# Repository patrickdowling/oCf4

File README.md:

# OC + F4
For grins I made an F405-based Teensy replacement for [o\_C](https://github.com/patrickdowling/O_C).

It seemed like a good idea at the time and was an "excuse" to add F4 support to my F0 framework which then became
[stm32x](https://github.com/patrickdowling/stm32x).

The four-layer board is pretty tightly packed and tried to include everything and the kitchen sink (I2C, serial/MIDI, USB header...). There's even space for an SPI flash chip on the bottom... It should also be noted that I'm really just winging it when it comes to hardware design.

The single point of annoyance (the shared SPI between the DAC and screen) however remains although it is possible to run the thing at closer to 30KHz here (the Teensy 3.2 on `o_C` was effectively maxxing out at 16.6KHz with the 30MHz SPI).

Utlimately though, once the base drivers (ADC/TR/DAC/screen) were working it didn't actually have a purpose so there's very little actual functionality. Except a very early draft of what might be a "better" framework. So here it is anyway, warts
and all.

If someone does want to pursue this further, let me know.

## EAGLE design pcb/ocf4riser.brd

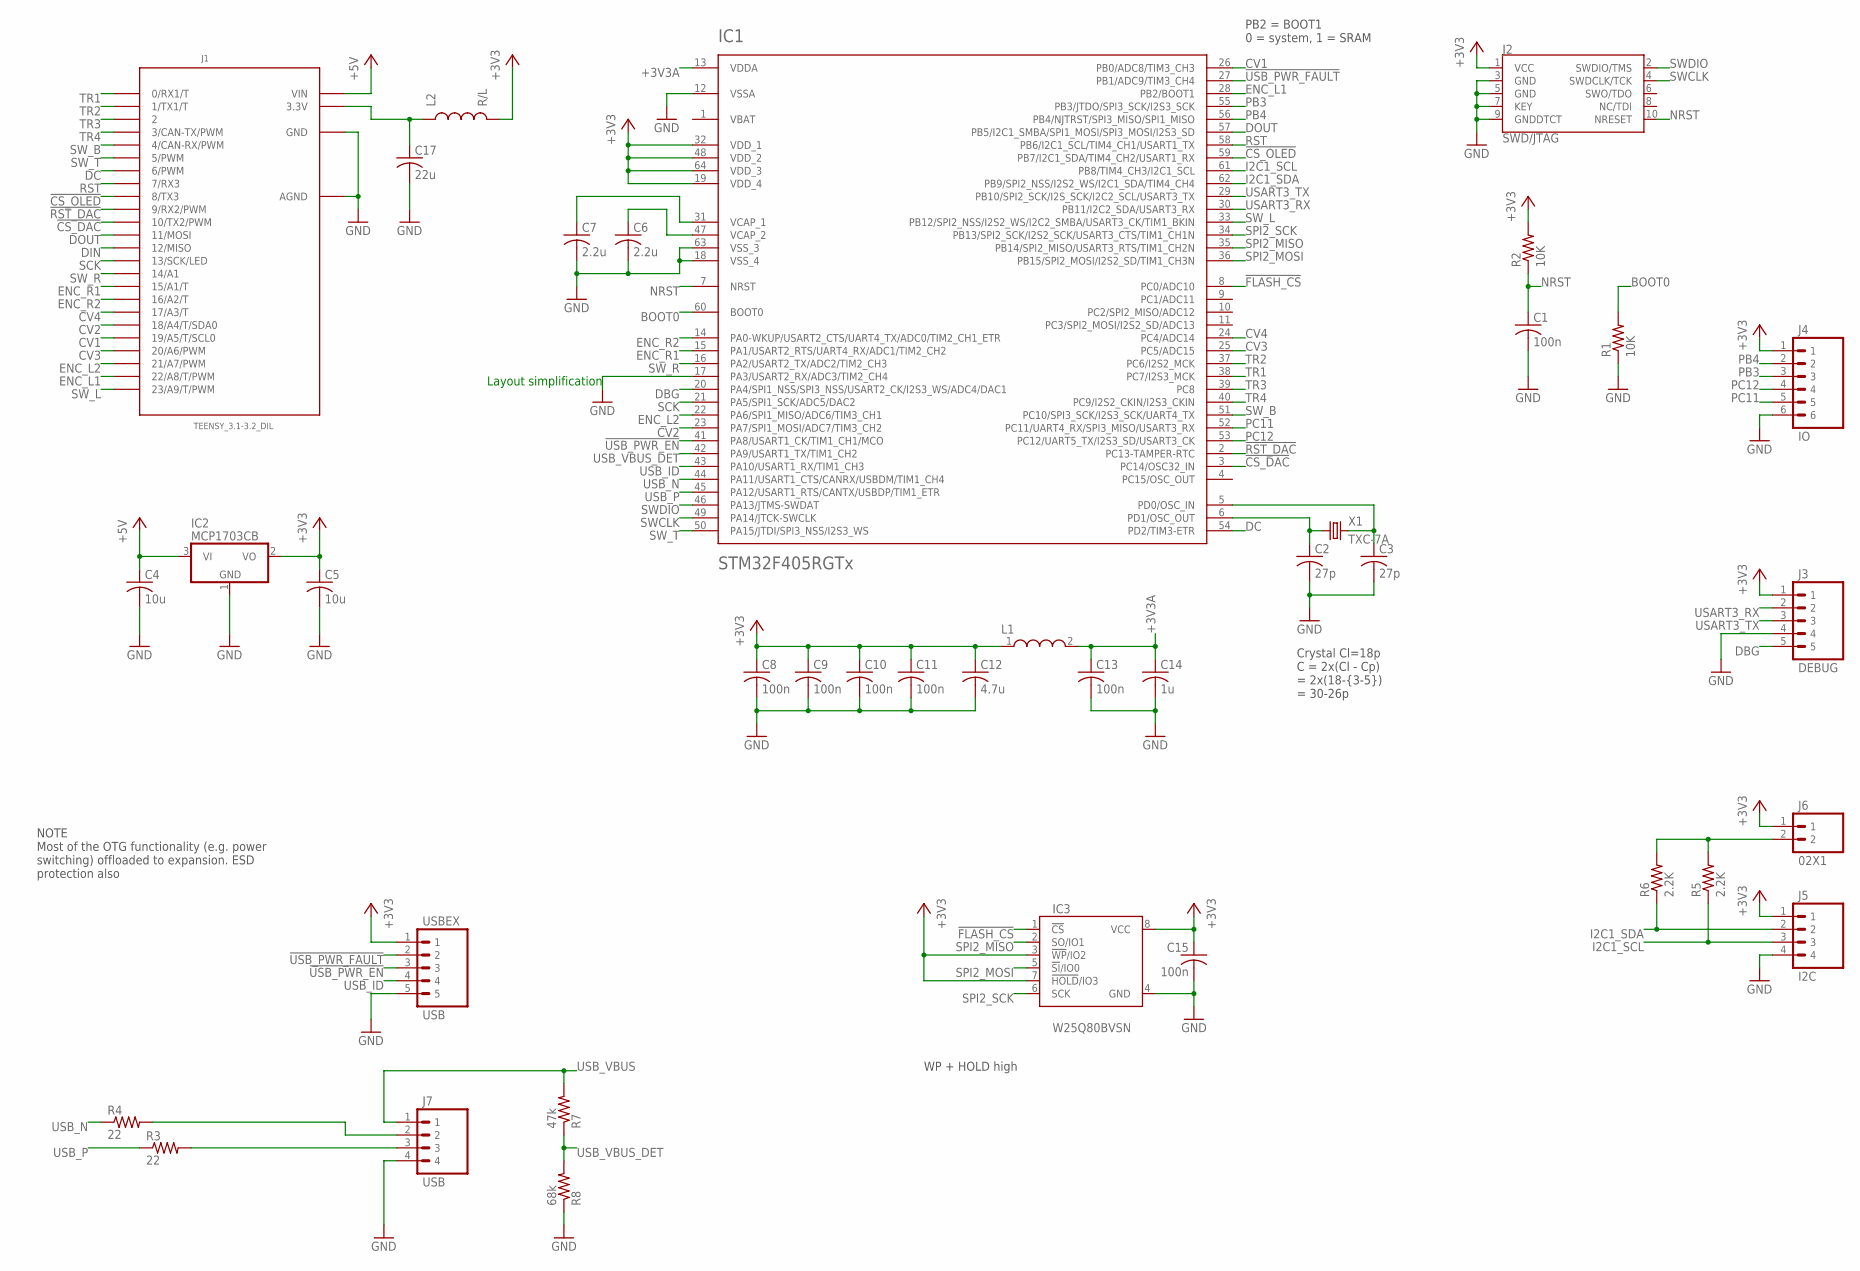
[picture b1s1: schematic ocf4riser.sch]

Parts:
C1, C8, C9, C10, C11, C13, C15: 100n; C0402
C2, C3: 27p; C0402
C4, C5: 10u; C0805
C6, C7: 2.2u; C0603
C12: 4.7u; C0603
C14: 1u; C0603
C17: 22u; C0805
IC1: STM32F405RGTx; TQFP-10X10-64
IC2: MCP1703CB; SOT23
IC3: W25Q80BVSN; SOIC-8
J1: TEENSY_3.1-3.2_DIL; TEENSY_3.0-3.2&LC_DIL
J2: SWD/JTAG; 2X5-1.27
J3: DEBUG; 05X1-THIN
J4: IO; 06X1-THIN
J5: I2C; 04X1-THIN
J6: 02X1; 02X1-THIN
J7: USB; 04X1-THIN
L1: WE-CBF_0603(WB/HS); WE-CBF_0603(W=2.2)
L2: R/L; 0805
R1, R2: 10K; R0402
R3, R4: 22; R0402
R5, R6: 2.2K; R0603
R7: 47k; R0402
R8: 68k; R0402
USBEX: USB; 05X1-THIN
X1: TXC-7A; CRYSTAL-TXC-7A

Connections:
!CS_DAC: IC1.3 (PC14/OSC32_IN), J1.10 (10/TX2/PWM)
!CS_OLED: IC1.59 (PB7/I2C1_SDA/TIM4_CH2/USART1_RX), J1.8 (8/TX3)
!FLASH_CS: IC1.8 (PC0/ADC10), IC3.1 (!CS!)
!RST_DAC: IC1.2 (PC13-TAMPER-RTC), J1.9 (9/RX2/PWM)
!USB_PWR_EN: IC1.41 (PA8/USART1_CK/TIM1_CH1/MCO), USBEX.3
!USB_PWR_FAULT: IC1.27 (PB1/ADC9/TIM3_CH4), USBEX.2
+3V3: C5.1, C8.1, C9.1, C10.1, C11.1, C12.1, C15.1, IC1.19 (VDD_4), IC1.32 (VDD_1), IC1.48 (VDD_2), IC1.64 (VDD_3), IC2.2 (VO), IC3.3 (!WP!/IO2), IC3.7 (!HOLD!/IO3), IC3.8 (VCC), J2.1 (VCC), J3.1, J4.1, J5.1, J6.1, L1.1, L2.2, R2.2, USBEX.1
+3V3A: C13.1, C14.1, IC1.13 (VDDA), L1.2
+5V: C4.1, IC2.3 (VI), J1.VIN
BOOT0: IC1.60 (BOOT0), R1.2
CV1: IC1.26 (PB0/ADC8/TIM3_CH3), J1.19/A5 (19/A5/T/SCL0)
CV2: IC1.23 (PA7/SPI1_MOSI/ADC7/TIM3_CH2), J1.18/A4 (18/A4/T/SDA0)
CV3: IC1.25 (PC5/ADC15), J1.20/A6 (20/A6/PWM)
CV4: IC1.24 (PC4/ADC14), J1.17/A3 (17/A3/T)
DBG: IC1.20 (PA4/SPI1_NSS/SPI3_NSS/USART2_CK/I2S3_WS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), J3.5
DC: IC1.54 (PD2/TIM3-ETR), J1.6 (6/PWM)
DIN: J1.12 (12/MISO)
DOUT: IC1.57 (PB5/I2C1_SMBA/SPI1_MOSI/SPI3_MOSI/I2S3_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), J1.11 (11/MOSI)
ENC_L1: IC1.28 (PB2/BOOT1), J1.22/A8 (22/A8/T/PWM)
ENC_L2: IC1.22 (PA6/SPI1_MISO/ADC6/TIM3_CH1), J1.21/A7 (21/A7/PWM)
ENC_R1: IC1.15 (PA1/USART2_RTS/UART4_RX/ADC1/TIM2_CH2), J1.15/A1 (15/A1/T)
ENC_R2: IC1.14 (PA0-WKUP/USART2_CTS/UART4_TX/ADC0/TIM2_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), J1.16/A2 (16/A2/T)
GND: C1.2, C2.2, C3.2, C4.2, C5.2, C6.2, C7.2, C8.2, C9.2, C10.2, C11.2, C12.2, C13.2, C14.2, C15.2, C17.2, IC1.12 (VSSA), IC1.17 (PA3/USART2_RX/ADC3/TIM2_CH4), IC1.18 (VSS_4), IC1.63 (VSS_3), IC2.1 (GND), IC3.4 (GND), J1.AGND, J1.GND, J2.3 (GND), J2.5 (GND), J2.7 (KEY), J2.9 (GNDDTCT), J3.4, J4.6, J5.4, J7.4, R1.1, R8.1, USBEX.5
I2C1_SCL: IC1.61 (PB8/TIM4_CH3/I2C1_SCL), J5.3, R5.1
I2C1_SDA: IC1.62 (PB9/SPI2_NSS/I2S2_WS/I2C1_SDA/TIM4_CH4), J5.2, R6.1
I2C_PU: J6.2, R5.2, R6.2
unnamed: C17.1, J1.3.3V, L2.1
unnamed: C3.1, IC1.5 (PD0/OSC_IN), X1.P$2 (2)
unnamed: C2.1, IC1.6 (PD1/OSC_OUT), X1.P$1 (1)
NRST: C1.1, IC1.7 (NRST), J2.10 (NRESET), R2.1
PB3: IC1.55 (PB3/JTDO/SPI3_SCK/I2S3_SCK), J4.3
PB4: IC1.56 (PB4/NJTRST/SPI3_MISO/SPI1_MISO), J4.2
PC11: IC1.52 (PC11/UART4_RX/SPI3_MISO/USART3_RX), J4.5
PC12: IC1.53 (PC12/UART5_TX/I2S3_SD/USART3_CK), J4.4
RST: IC1.58 (PB6/I2C1_SCL/TIM4_CH1/USART1_TX), J1.7 (7/RX3)
SCK: IC1.21 (PA5/SPI1_SCK/ADC5/DAC2), J1.13 (13/SCK/LED)
SPI2_MISO: IC1.35 (PB14/SPI2_MISO/USART3_RTS/TIM1_CH2N), IC3.2 (SO/IO1)
SPI2_MOSI: IC1.36 (PB15/SPI2_MOSI/I2S2_SD/TIM1_CH3N), IC3.5 (!SI!/IO0)
SPI2_SCK: IC1.34 (PB13/SPI2_SCK/I2S2_SCK/USART3_CTS/TIM1_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), IC3.6 (SCK)
SWCLK: IC1.49 (PA14/JTCK-SWCLK), J2.4 (SWDCLK/TCK)
SWDIO: IC1.46 (PA13/JTMS-SWDAT), J2.2 (SWDIO/TMS)
SW_B: IC1.51 (PC10/SPI3_SCK/I2S3_SCK/UART4_TX), J1.4 (4/CAN-RX/PWM)
SW_L: IC1.33 (PB12/SPI2_NSS/I2S2_WS/I2C2_SMBA/USART3_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), J1.23/A9 (23/A9/T/PWM)
SW_R: IC1.16 (PA2/USART2_TX/ADC2/TIM2_CH3), J1.14/A0 (14/A1)
SW_T: IC1.50 (PA15/JTDI/SPI3_NSS/I2S3_WS), J1.5 (5/PWM)
TR1: IC1.38 (PC7/I2S3_MCK), J1.0 (0/RX1/T)
TR2: IC1.37 (PC6/I2S2_MCK), J1.1 (1/TX1/T)
TR3: IC1.39 (PC8), J1.2
TR4: IC1.40 (PC9/I2S2_CKIN/I2S3_CKIN), J1.3 (3/CAN-TX/PWM)
USART3_RX: IC1.30 (PB11/I2C2_SDA/USART3_RX), J3.2
USART3_TX: IC1.29 (PB10/SPI2_SCK/I2S_SCK/I2C2_SCL/USART3_TX), J3.3
USB_ID: IC1.43 (PA10/USART1_RX/TIM1_CH3), USBEX.4
USB_I_N: J7.2, R4.2
USB_I_P: J7.3, R3.2
USB_N: IC1.44 (PA11/USART1_CTS/CANRX/USBDM/TIM1_CH4), R4.1
USB_P: IC1.45 (PA12/USART1_RTS/CANTX/USBDP/TIM1_ETR), R3.1
USB_VBUS: J7.1, R7.2
USB_VBUS_DET: IC1.42 (PA9/USART1_TX/TIM1_CH2), R7.1, R8.2
VBAT: IC1.1 (VBAT)
VCAP_1: C7.1, IC1.31 (VCAP_1)
VCAP_2: C6.1, IC1.47 (VCAP_2)

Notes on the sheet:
Layout simplification
PB2 = BOOT1 0 = system, 1 = SRAM
WP + HOLD high
NOTE Most of the OTG functionality (e.g. power switching) offloaded to expansion. ESD protection also
Crystal Cl=18p C = 2x(Cl - Cp) = 2x(18-{3-5}) = 30-26p

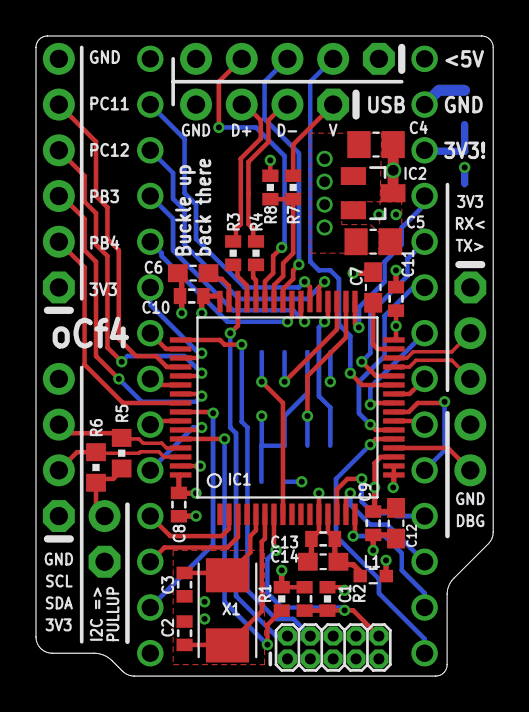
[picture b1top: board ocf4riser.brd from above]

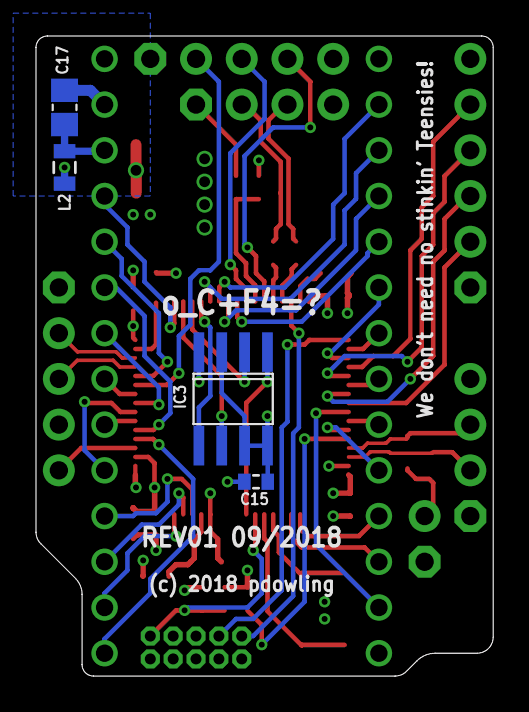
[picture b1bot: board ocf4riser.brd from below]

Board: 4 copper layers, 25.4 x 35.6 mm, 38 parts (4 on the bottom side), 59 nets.

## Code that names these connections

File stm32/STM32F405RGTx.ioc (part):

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Mcu.Name=STM32F405RGTx
Mcu.Package=LQFP64
Mcu.UserName=STM32F405RGTx
PA0-WKUP.GPIOParameters=GPIO_Label
PA0-WKUP.GPIO_Label=ENC_R2
PA0-WKUP.Signal=GPIO_Input
PA1.GPIOParameters=GPIO_Label
PA1.GPIO_Label=ENC_R1
PA1.Signal=GPIO_Input
PA10.Mode=OTG/Dual_Role_Device
PA10.Signal=USB_OTG_FS_ID
PA11.Mode=OTG/Dual_Role_Device
PA11.Signal=USB_OTG_FS_DM
PA12.Mode=OTG/Dual_Role_Device
PA12.Signal=USB_OTG_FS_DP
PA13.Mode=Serial_Wire
PA13.Signal=SYS_JTMS-SWDIO
PA14.Mode=Serial_Wire
PA14.Signal=SYS_JTCK-SWCLK
PA15.GPIOParameters=GPIO_Label
PA15.GPIO_Label=SW_T
PA15.Signal=GPIO_Input
PA2.GPIOParameters=GPIO_Label
PA2.GPIO_Label=SW_R
PA2.Signal=GPIO_Input
PA3.GPIOParameters=GPIO_Label
PA3.GPIO_Label=GND
PA3.Signal=GPIO_Input
PA4.GPIOParameters=GPIO_Label
PA4.GPIO_Label=DBG
PA4.Signal=GPIO_Output
PA5.Mode=TX_Only_Simplex_Unidirect_Master
PA5.Signal=SPI1_SCK
PA6.GPIOParameters=GPIO_Label
PA6.GPIO_Label=ENC_L2
PA6.Signal=GPIO_Input
PA7.GPIOParameters=GPIO_Label
PA7.GPIO_Label=CV2
PA7.Signal=ADCx_IN7
PA8.GPIOParameters=GPIO_Label
PA8.GPIO_Label=USB_PWR_EN
PA8.Signal=GPIO_Output
PA9.GPIOParameters=GPIO_Label
PA9.GPIO_Label=USB_OTG_FS_VBUS
PA9.Signal=GPIO_Input
PB0.GPIOParameters=GPIO_Label
PB0.GPIO_Label=CV1
PB0.Signal=ADCx_IN8
PB1.GPIOParameters=GPIO_Label
PB1.GPIO_Label=USB_PWR_FAULT
PB1.Signal=GPIO_Input
PB10.Mode=Asynchronous
PB10.Signal=USART3_TX
PB11.Mode=Asynchronous
PB11.Signal=USART3_RX
PB12.GPIOParameters=GPIO_Label
PB12.GPIO_Label=SW_L
PB12.Signal=GPIO_Input
PB13.Mode=Full_Duplex_Master
PB13.Signal=SPI2_SCK
PB14.Mode=Full_Duplex_Master
PB14.Signal=SPI2_MISO
PB15.Mode=Full_Duplex_Master
PB15.Signal=SPI2_MOSI
PB2.GPIOParameters=GPIO_Label
PB2.GPIO_Label=ENC_L1
PB2.Signal=GPIO_Input
PB3.GPIOParameters=GPIO_Label
PB3.GPIO_Label=PB3
PB3.Signal=GPIO_Output
PB4.GPIOParameters=GPIO_Label
PB4.GPIO_Label=PB4
PB4.Signal=GPIO_Output
PB5.Mode=TX_Only_Simplex_Unidirect_Master
PB5.Signal=SPI1_MOSI
PB6.GPIOParameters=GPIO_Label
PB6.GPIO_Label=RST
PB6.Signal=GPIO_Output
PB7.GPIOParameters=GPIO_Label
PB7.GPIO_Label=CS_OLED
PB7.Signal=GPIO_Output
PB8.Mode=I2C
PB8.Signal=I2C1_SCL
PB9.Mode=I2C
PB9.Signal=I2C1_SDA
PC0.GPIOParameters=GPIO_Label
PC0.GPIO_Label=FLASH_CS
PC0.Signal=GPIO_Output
PC10.GPIOParameters=GPIO_Label
PC10.GPIO_Label=SW_B
PC10.Signal=GPIO_Input
PC11.GPIOParameters=GPIO_Label
PC11.GPIO_Label=PC11
PC11.Signal=GPIO_Output
PC12.GPIOParameters=GPIO_Label
PC12.GPIO_Label=PC12
PC12.Signal=GPIO_Output
PC13-ANTI_TAMP.GPIOParameters=GPIO_Label
PC13-ANTI_TAMP.GPIO_Label=RST_DAC
PC13-ANTI_TAMP.Signal=GPIO_Output
PC14-OSC32_IN.GPIOParameters=GPIO_Label
PC14-OSC32_IN.GPIO_Label=CS_DAC
PC14-OSC32_IN.Signal=GPIO_Output
PC4.GPIOParameters=GPIO_Label
PC4.GPIO_Label=CV4
PC4.Signal=ADCx_IN14
PC5.GPIOParameters=GPIO_Label
PC5.GPIO_Label=CV3
PC5.Signal=ADCx_IN15
PC6.GPIOParameters=GPIO_Label
PC6.GPIO_Label=TR2
PC6.Signal=S_TIM3_CH1
PC7.GPIOParameters=GPIO_Label
PC7.GPIO_Label=TR1
PC7.Signal=S_TIM3_CH2
PC8.GPIOParameters=GPIO_Label
PC8.GPIO_Label=TR3
PC8.Signal=S_TIM3_CH3
PC9.GPIOParameters=GPIO_Label
PC9.GPIO_Label=TR4
PC9.Signal=S_TIM3_CH4
PD2.GPIOParameters=GPIO_Label
PD2.GPIO_Label=DC
PD2.Signal=GPIO_Output
PH0-OSC_IN.Mode=HSE-External-Oscillator
PH0-OSC_IN.Signal=RCC_OSC_IN
PH1-OSC_OUT.Mode=HSE-External-Oscillator
PH1-OSC_OUT.Signal=RCC_OSC_OUT
RCC.HSE_VALUE=8000000
RCC.SYSCLKFreq_VALUE=168000000
RCC.SYSCLKSource=RCC_SYSCLKSOURCE_PLLCLK

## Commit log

2018-09-02 Pin headers, values & names
2018-09-04 Tweaks
2018-09-08 USB as header instead of receptacle
2018-09-30 Skeleton firmware using stm32x, display driver somewhat functional
2018-09-30 Initial support for DAC, core update timer
2018-09-30 ADC driver skeleton
2018-10-03 Introducing IOFrame
2018-10-03 UI prep
2018-10-09 Skeleton patch infrastructure, ADC experiments with oversampling
2018-10-10 Fix DAC CS pin, tweak ADC, misc
2018-10-14 Steps towards patch/processor/ui framework, misc
2018-10-15 Misc UI
2018-10-16 WIP menu/ui/patch
2018-10-21 Use concrete type for pooled instantiations, update stm32x
2018-11-13 Back to 0 warnings
2021-12-04 Add readme

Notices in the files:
pcb/ocf4riser.brd:
(c) 2018 pdowling
parts and their libraries:
EagleLibrary_Wuerth_Elektronik_eiSos_rev: Copyright: Würth Elektronik
SparkFun-Passives: Licensing: Creative Commons ShareAlike 4.0 International - https://creativecommons.org/licenses/by-sa/4.0
